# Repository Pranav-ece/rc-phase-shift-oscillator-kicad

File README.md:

RC Phase Shift Oscillator (KiCad)

Description
This file demonstrates the design and simulation of an RC Phase Shift Oscillator using KiCad. 
Theory
An RC Phase Shift Oscillator works on the principle of phase shift:
- Each RC stage provides 60° phase shift
- Total from 3 stages = 180°
- Op-amp provides additional 180°
- Total phase shift = 360° → sustained oscillations

Tools Used
- KiCad (Schematic design)

 Learning Outcome
- Understood oscillator design principles
- Learned feedback and phase shift conditions

Future Improvements
- PCB design of the circuit
- Hardware implementation using op-amp IC

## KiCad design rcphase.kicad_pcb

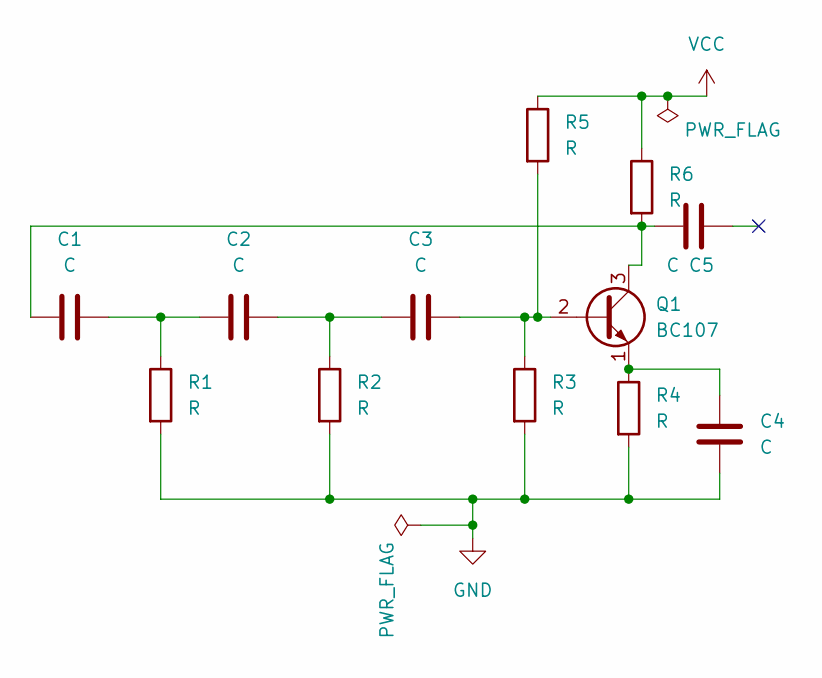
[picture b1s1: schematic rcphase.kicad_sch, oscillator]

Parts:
C1, C2, C3, C4, C5: C; C_Radial_D5.0mm_H11.0mm_P2.00mm
Q1: BC107; TO-18-3
R1, R2, R3, R4, R5, R6: R; R_2512_6332Metric

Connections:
GND: C4.1, R1.2, R2.2, R3.2, R4.2
unnamed: C1.2, C2.1, R1.1
unnamed: C2.2, C3.1, R2.1
unnamed: C3.2, Q1.2 (B), R3.1, R5.2
unnamed: C1.1, C5.1, Q1.3 (C), R6.2
unnamed: C4.2, Q1.1 (E), R4.1
VCC: R5.1, R6.1

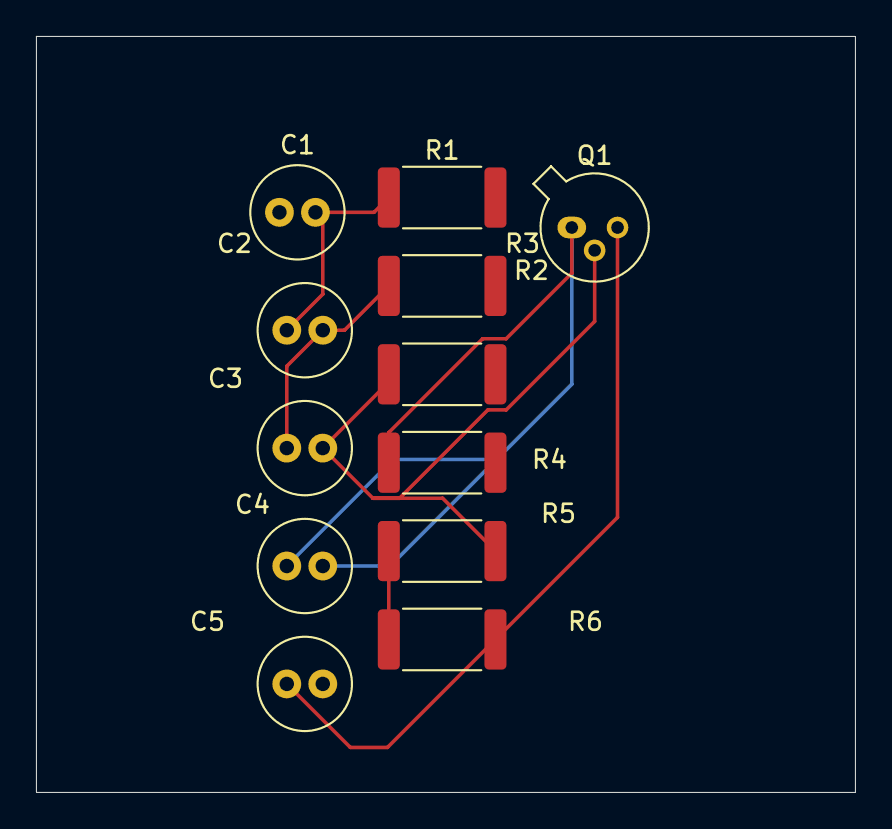
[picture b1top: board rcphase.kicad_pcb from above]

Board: 2 copper layers, 45.5 x 42.0 mm, 12 parts (0 on the bottom side), 7 nets.

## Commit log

2026-03-18 Add files via upload
    Schematic of circuit
2026-03-18 Add files via upload
    PCB desgin
2026-03-18 kicad file
2026-03-18 Add files via upload
    gbr files
